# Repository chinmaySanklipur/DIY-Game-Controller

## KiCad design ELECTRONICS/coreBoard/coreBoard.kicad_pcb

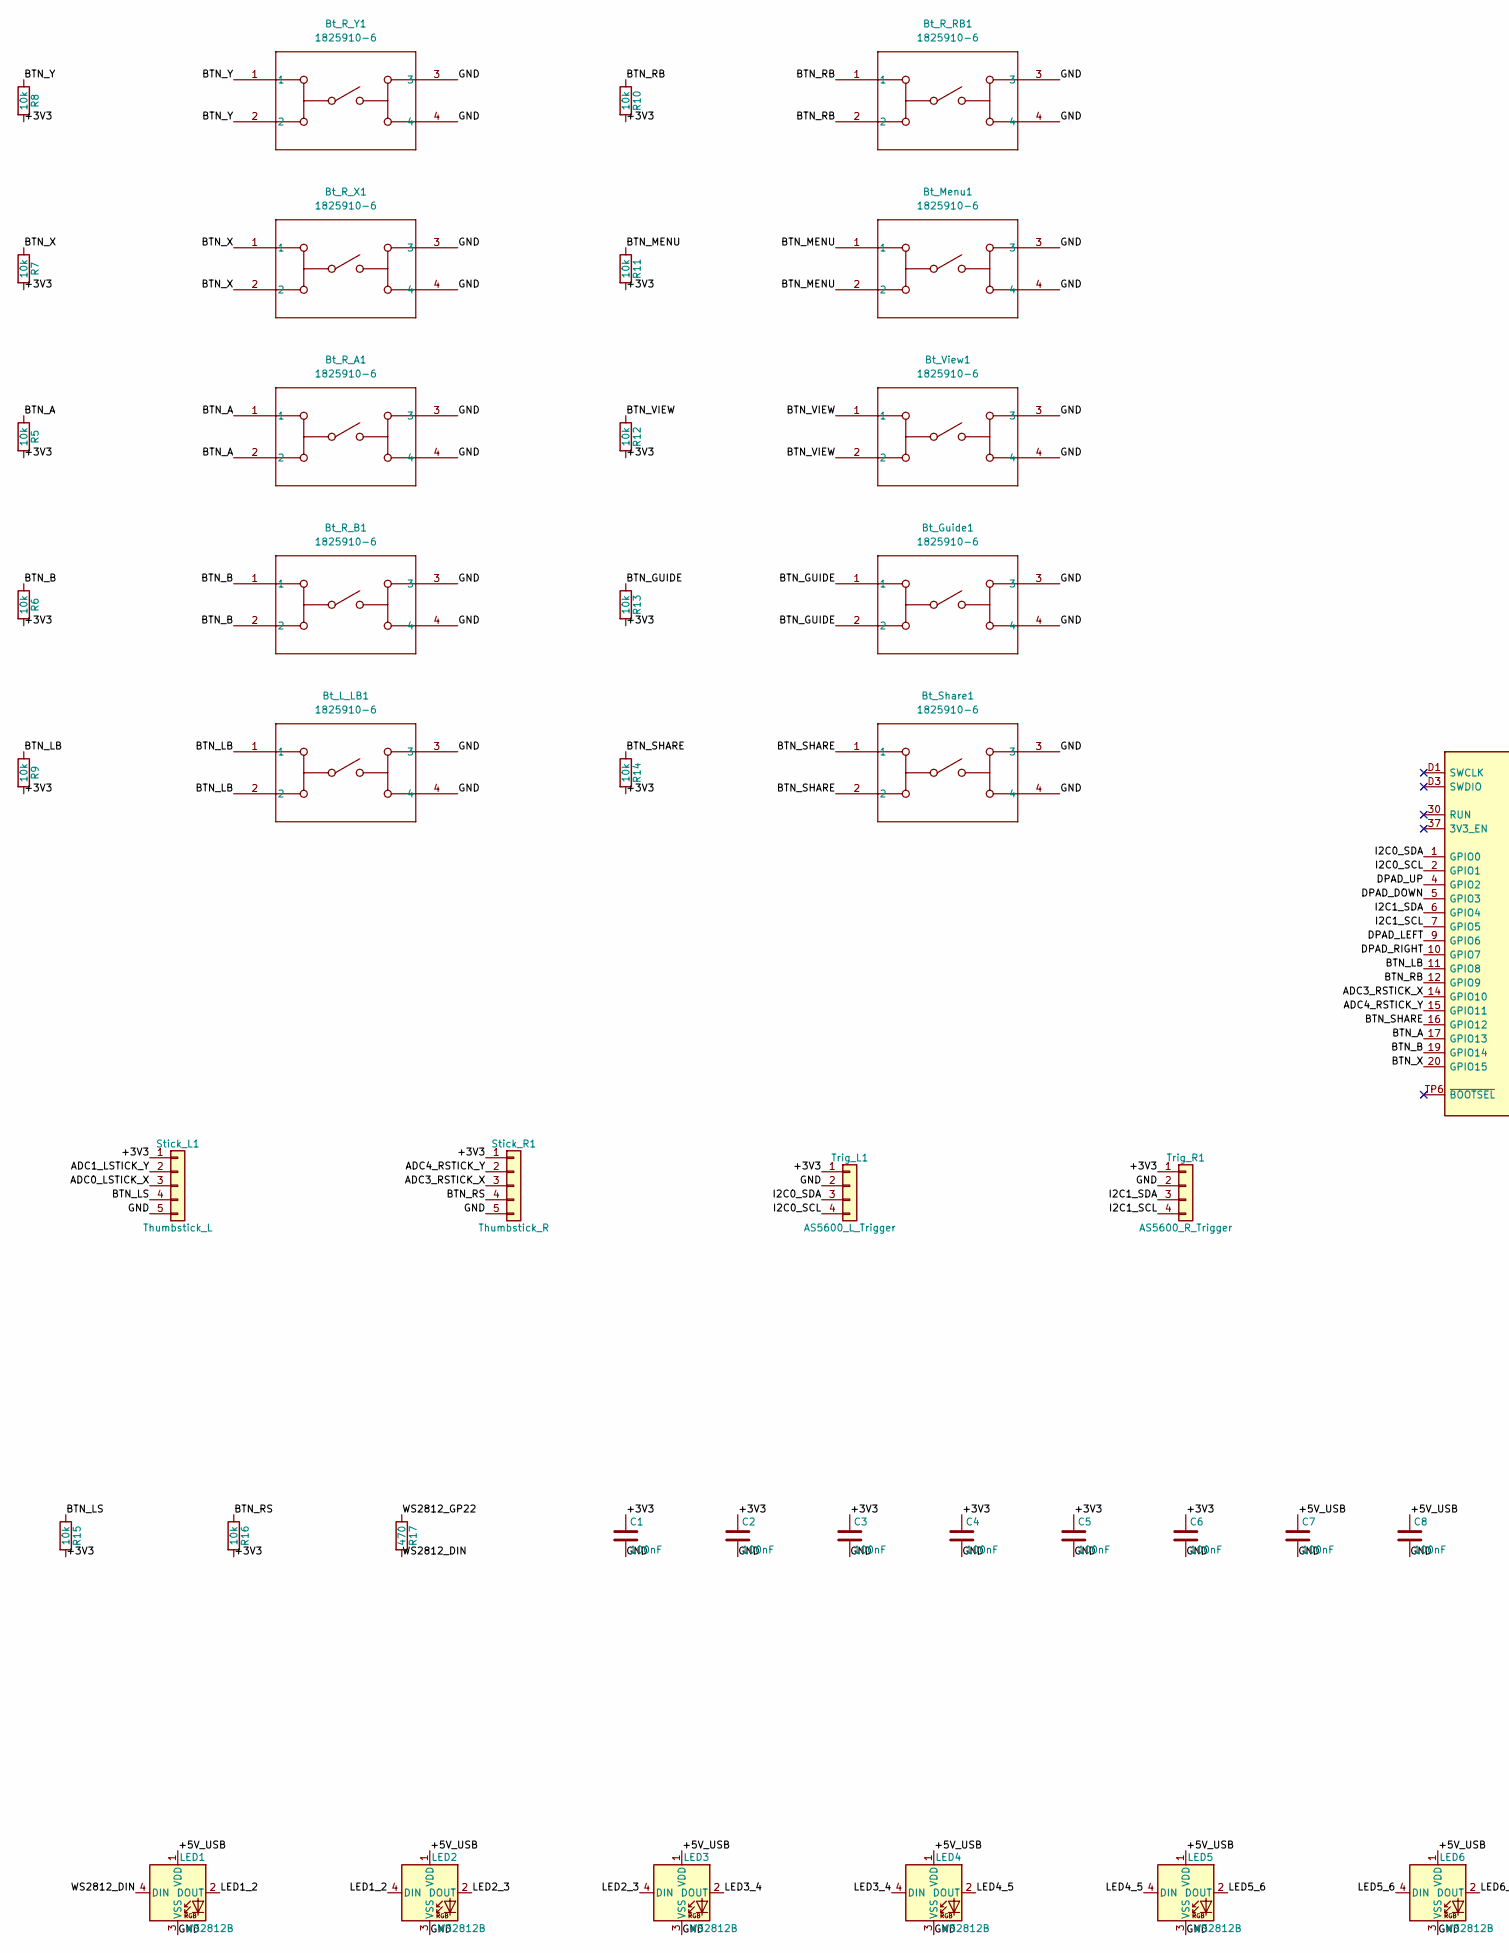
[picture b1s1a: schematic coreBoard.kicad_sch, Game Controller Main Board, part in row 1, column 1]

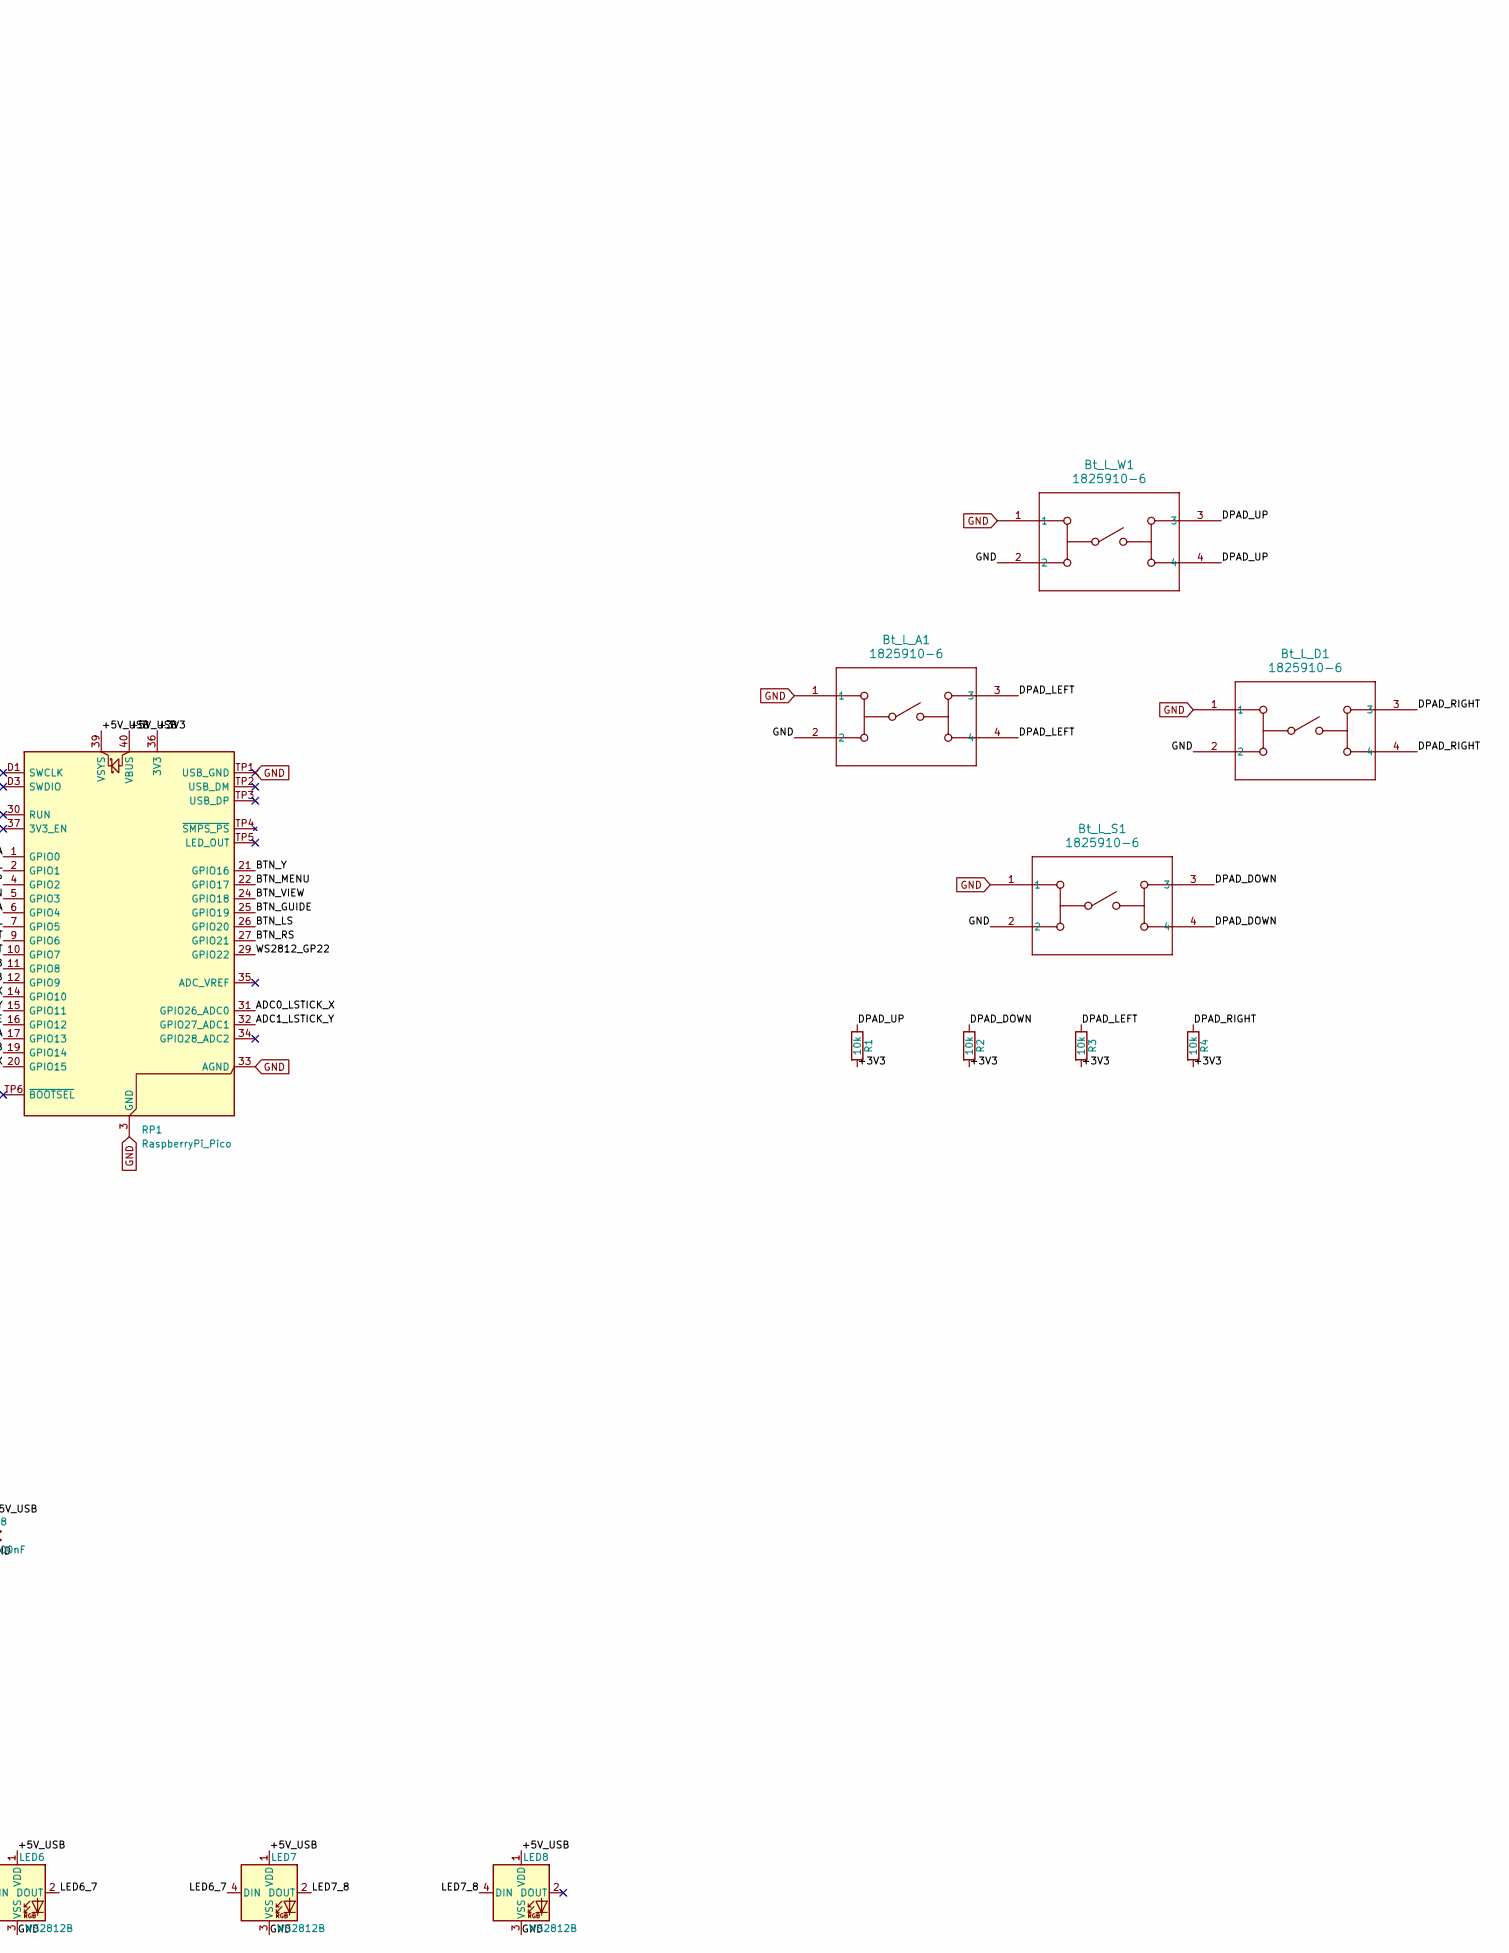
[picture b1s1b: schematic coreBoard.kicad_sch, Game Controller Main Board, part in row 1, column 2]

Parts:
Bt_Guide1: 1825910-6; SW4_1825910-B_TEC
Bt_L_A1: 1825910-6; SW4_1825910-B_TEC
Bt_L_D1: 1825910-6; SW4_1825910-B_TEC
Bt_L_LB1: 1825910-6; SW4_1825910-B_TEC
Bt_L_S1: 1825910-6; SW4_1825910-B_TEC
Bt_L_W1: 1825910-6; SW4_1825910-B_TEC
Bt_Menu1: 1825910-6; SW4_1825910-B_TEC
Bt_R_A1: 1825910-6; SW4_1825910-B_TEC
Bt_R_B1: 1825910-6; SW4_1825910-B_TEC
Bt_R_RB1: 1825910-6; SW4_1825910-B_TEC
Bt_R_X1: 1825910-6; SW4_1825910-B_TEC
Bt_R_Y1: 1825910-6; SW4_1825910-B_TEC
Bt_Share1: 1825910-6; SW4_1825910-B_TEC
Bt_View1: 1825910-6; SW4_1825910-B_TEC
C1, C2, C3, C4, C5, C6, C7, C8: 100nF; C_Disc_D5.0mm_W2.5mm_P5.00mm
LED1, LED2, LED3, LED4, LED5, LED6, LED7, LED8: WS2812B; LED_D5.0mm-4_RGB
R1, R2, R3, R4, R5, R6, R7, R8, R9, R10, R11, R12, R13, R14, R15, R16: 10k; R_Axial_DIN0207_L6.3mm_D2.5mm_P10.16mm_Horizontal
R17: 470; R_Axial_DIN0207_L6.3mm_D2.5mm_P10.16mm_Horizontal
RP1: RaspberryPi_Pico; RaspberryPi_Pico_SMD
Stick_L1: Thumbstick_L; PinHeader_1x05_P2.54mm_Vertical
Stick_R1: Thumbstick_R; PinHeader_1x05_P2.54mm_Vertical
Trig_L1: AS5600_L_Trigger; PinHeader_1x04_P2.54mm_Vertical
Trig_R1: AS5600_R_Trigger; PinHeader_1x04_P2.54mm_Vertical

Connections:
/+3V3: C1.1, C2.1, C3.1, C4.1, C5.1, C6.1, R1.2, R2.2, R3.2, R4.2, R5.2, R6.2, R7.2, R8.2, R9.2, R10.2, R11.2, R12.2, R13.2, R14.2, R15.2, R16.2, RP1.36 (3V3), Stick_L1.1, Stick_R1.1, Trig_L1.1, Trig_R1.1
/+5V_USB: C7.1, C8.1, LED1.1 (VDD), LED2.1 (VDD), LED3.1 (VDD), LED4.1 (VDD), LED5.1 (VDD), LED6.1 (VDD), LED7.1 (VDD), LED8.1 (VDD), RP1.39 (VSYS), RP1.40 (VBUS)
/ADC0_LSTICK_X: RP1.31 (GPIO26_ADC0), Stick_L1.3
/ADC1_LSTICK_Y: RP1.32 (GPIO27_ADC1), Stick_L1.2
/ADC3_RSTICK_X: RP1.14 (GPIO10), Stick_R1.3
/ADC4_RSTICK_Y: RP1.15 (GPIO11), Stick_R1.2
/BTN_A: Bt_R_A1.1, Bt_R_A1.2, R5.1, RP1.17 (GPIO13)
/BTN_B: Bt_R_B1.1, Bt_R_B1.2, R6.1, RP1.19 (GPIO14)
/BTN_GUIDE: Bt_Guide1.1, Bt_Guide1.2, R13.1, RP1.25 (GPIO19)
/BTN_LB: Bt_L_LB1.1, Bt_L_LB1.2, R9.1, RP1.11 (GPIO8)
/BTN_LS: R15.1, RP1.26 (GPIO20), Stick_L1.4
/BTN_MENU: Bt_Menu1.1, Bt_Menu1.2, R11.1, RP1.22 (GPIO17)
/BTN_RB: Bt_R_RB1.1, Bt_R_RB1.2, R10.1, RP1.12 (GPIO9)
/BTN_RS: R16.1, RP1.27 (GPIO21), Stick_R1.4
/BTN_SHARE: Bt_Share1.1, Bt_Share1.2, R14.1, RP1.16 (GPIO12)
/BTN_VIEW: Bt_View1.1, Bt_View1.2, R12.1, RP1.24 (GPIO18)
/BTN_X: Bt_R_X1.1, Bt_R_X1.2, R7.1, RP1.20 (GPIO15)
/BTN_Y: Bt_R_Y1.1, Bt_R_Y1.2, R8.1, RP1.21 (GPIO16)
/DPAD_DOWN: Bt_L_S1.3, Bt_L_S1.4, R2.1, RP1.5 (GPIO3)
/DPAD_LEFT: Bt_L_A1.3, Bt_L_A1.4, R3.1, RP1.9 (GPIO6)
/DPAD_RIGHT: Bt_L_D1.3, Bt_L_D1.4, R4.1, RP1.10 (GPIO7)
/DPAD_UP: Bt_L_W1.3, Bt_L_W1.4, R1.1, RP1.4 (GPIO2)
/I2C0_SCL: RP1.2 (GPIO1), Trig_L1.4
/I2C0_SDA: RP1.1 (GPIO0), Trig_L1.3
/I2C1_SCL: RP1.7 (GPIO5), Trig_R1.4
/I2C1_SDA: RP1.6 (GPIO4), Trig_R1.3
/LED1_2: LED1.2 (DOUT), LED2.4 (DIN)
/LED2_3: LED2.2 (DOUT), LED3.4 (DIN)
/LED3_4: LED3.2 (DOUT), LED4.4 (DIN)
/LED4_5: LED4.2 (DOUT), LED5.4 (DIN)
/LED5_6: LED5.2 (DOUT), LED6.4 (DIN)
/LED6_7: LED6.2 (DOUT), LED7.4 (DIN)
/LED7_8: LED7.2 (DOUT), LED8.4 (DIN)
/WS2812_DIN: LED1.4 (DIN), R17.2
/WS2812_GP22: R17.1, RP1.29 (GPIO22)
GND: Bt_Guide1.3, Bt_Guide1.4, Bt_L_A1.1, Bt_L_A1.2, Bt_L_D1.1, Bt_L_D1.2, Bt_L_LB1.3, Bt_L_LB1.4, Bt_L_S1.1, Bt_L_S1.2, Bt_L_W1.1, Bt_L_W1.2, Bt_Menu1.3, Bt_Menu1.4, Bt_R_A1.3, Bt_R_A1.4, Bt_R_B1.3, Bt_R_B1.4, Bt_R_RB1.3, Bt_R_RB1.4, Bt_R_X1.3, Bt_R_X1.4, Bt_R_Y1.3, Bt_R_Y1.4, Bt_Share1.3, Bt_Share1.4, Bt_View1.3, Bt_View1.4, C1.2, C2.2, C3.2, C4.2, C5.2, C6.2, C7.2, C8.2, LED1.3 (VSS), LED2.3 (VSS), LED3.3 (VSS), LED4.3 (VSS), LED5.3 (VSS), LED6.3 (VSS), LED7.3 (VSS), LED8.3 (VSS), RP1.3 (GND), RP1.8 (GND), RP1.13 (GND), RP1.18 (GND), RP1.23 (GND), RP1.28 (GND), RP1.33 (AGND), RP1.38 (GND), RP1.D2 (GND), RP1.TP1 (USB_GND), Stick_L1.5, Stick_R1.5, Trig_L1.2, Trig_R1.2

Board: 2 copper layers, 52 parts (0 on the bottom side), 36 nets, no tracks yet.

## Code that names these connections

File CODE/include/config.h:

/**
 * @file config.h
 * @brief Central configuration: GPIO pin assignments, timing, and tunable constants.
 *
 * Edit this file to remap pins or change deadzone/lighting behaviour.
 * Every other source file includes this header so changes here propagate
 * automatically at build time.
 *
 * Pin assignments mirror the KiCad schematic (game_controller.kicad_sch).
 * Net names in comments match schematic net labels for easy cross-reference.
 */

#ifndef CONFIG_H
#define CONFIG_H

#include "pico/stdlib.h"

/* ─────────────────────────────────────────────────────────────────────────────
 * GPIO — Digital Buttons
 * All buttons are active-LOW (pulled HIGH internally; pressed = connected to GND)
 * ───────────────────────────────────────────────────────────────────────────── */

/** Face buttons — schematic nets BTN_A … BTN_Y */
#define PIN_BTN_A       13   /* GP13 */
#define PIN_BTN_B       14   /* GP14 */
#define PIN_BTN_X       15   /* GP15 */
#define PIN_BTN_Y       16   /* GP16 */

/** D-pad — schematic nets DPAD_UP … DPAD_RIGHT */
#define PIN_DPAD_UP      2   /* GP2  */
#define PIN_DPAD_DN      3   /* GP3  */
#define PIN_DPAD_LEFT    6   /* GP6  */
#define PIN_DPAD_RIGHT   7   /* GP7  */

/** Bumpers — schematic nets BTN_LB / BTN_RB */
#define PIN_BTN_LB       8   /* GP8  */
#define PIN_BTN_RB       9   /* GP9  */

/** System buttons — schematic nets BTN_MENU / BTN_VIEW / BTN_GUIDE / BTN_SHARE */
#define PIN_BTN_MENU    17   /* GP17 */
#define PIN_BTN_VIEW    18   /* GP18 */
#define PIN_BTN_GUIDE   19   /* GP19 */
#define PIN_BTN_SHARE   12   /* GP12 */

/** Thumbstick click buttons — schematic nets BTN_LS / BTN_RS */
#define PIN_BTN_LS      20   /* GP20 */
#define PIN_BTN_RS      21   /* GP21 */

/* ─────────────────────────────────────────────────────────────────────────────
 * GPIO — Analog (ADC)
 * RP2040 ADC inputs are GP26-GP29.  Only GP26-GP28 are brought out on Pico.
 * Thumbstick axes are read on ADC0 and ADC1 (left stick).
 * ───────────────────────────────────────────────────────────────────────────── */

/** Left stick — schematic nets ADC0_LSTICK_X / ADC1_LSTICK_Y */
#define PIN_LSTICK_X    26   /* GP26 / ADC0 */
#define PIN_LSTICK_Y    27   /* GP27 / ADC1 */
#define ADC_LSTICK_X     0   /* ADC channel index for GP26 */
#define ADC_LSTICK_Y     1   /* ADC channel index for GP27 */

/**
 * Right stick — the Pico only exposes ADC on GP26-GP28, so the right stick
 * connects to GP10/GP11 read via external circuitry.  For this firmware we
 * treat these as the same two ADC channels multiplexed or read via the second
 * pair of physical lines.  Adjust if hardware differs.
 */
#define PIN_RSTICK_X    10   /* GP10 — right stick horizontal */
#define PIN_RSTICK_Y    11   /* GP11 — right stick vertical   */
/* Note: GP10/GP11 are NOT native ADC pins on RP2040.
 * If using a resistor-ladder or MCP3204 for right stick, replace ADC reads
 * in inputs.c with the appropriate SPI/I2C reads.
 * For a direct wiring option, swap thumbstick to GP26/GP27 for left and
 * route right stick via an external ADC IC. */

/* ─────────────────────────────────────────────────────────────────────────────
 * GPIO — I2C for AS5600 hall-effect trigger sensors
 * I2C0 → Left trigger  (U2, address 0x36)
 * I2C1 → Right trigger (U3, address 0x36 — separate bus avoids conflict)
 * ───────────────────────────────────────────────────────────────────────────── */

#define PIN_I2C0_SDA     0   /* GP0  — I2C0_SDA → U2 */
#define PIN_I2C0_SCL     1   /* GP1  — I2C0_SCL → U2 */
#define PIN_I2C1_SDA     4   /* GP4  — I2C1_SDA → U3 */
#define PIN_I2C1_SCL     5   /* GP5  — I2C1_SCL → U3 */

#define I2C_SPEED_HZ    400000   /* 400 kHz Fast-mode */
#define AS5600_ADDR     0x36     /* Fixed I2C address for AS5600 */
#define AS5600_REG_ANGLE_H 0x0C /* High byte of 12-bit raw angle */
#define AS5600_REG_ANGLE_L 0x0D /* Low  byte of 12-bit raw angle */

/* ─────────────────────────────────────────────────────────────────────────────
 * GPIO — WS2812B RGB LED data line
 * Uses PIO state machine so the CPU is never blocked during LED updates.
 * ───────────────────────────────────────────────────────────────────────────── */

#define PIN_WS2812      22   /* GP22 — WS2812_DIN through 470-ohm series R */
#define NUM_LEDS         8   /* LED1–LED8 in daisy-chain */
#define WS2812_PIO      pio0 /* Which PIO block to use */
#define WS2812_SM        0   /* State machine index within that PIO */

/* ─────────────────────────────────────────────────────────────────────────────
 * Deadzone and response-curve parameters
 * ───────────────────────────────────────────────────────────────────────────── */

/**
 * Inner circular deadzone radius as a fraction of the full stick range.
 * 0.08 = 8 % — deflections smaller than this produce zero output.
 * Prevents stick drift when the stick rests slightly off-centre.
 */
#define DEADZONE_INNER_FRAC   0.08f

/**
 * Outer clamp: values this close to maximum are treated as full deflection.
 * Compensates for sticks that do not mechanically reach true maximum.
 */
#define DEADZONE_OUTER_FRAC   0.97f

/**
 * Trigger inner dead-band: first N% of travel outputs zero.
 * Prevents accidental trigger input when the trigger rests slightly depressed.
 */
#define TRIGGER_INNER_FRAC    0.04f

/**
 * Trigger outer clamp: anything beyond this fraction is treated as fully pressed.
 */
#define TRIGGER_OUTER_FRAC    0.97f

/* ─────────────────────────────────────────────────────────────────────────────
 * ADC calibration storage keys in flash (littlefs)
 * ───────────────────────────────────────────────────────────────────────────── */

/** Path inside the littlefs volume where the config struct is stored */
#define CONFIG_FLASH_PATH  "/config.bin"

/** Magic number at start of stored config — detects uninitialised/corrupt data */
#define CONFIG_MAGIC  0xCAFE2026u

/* ─────────────────────────────────────────────────────────────────────────────
 * USB HID
 * ───────────────────────────────────────────────────────────────────────────── */

/** HID report interval in milliseconds (8 ms = 125 Hz, maximum for USB FS HID) */
#define HID_REPORT_INTERVAL_MS  8

/* ─────────────────────────────────────────────────────────────────────────────
 * Debounce
 * ───────────────────────────────────────────────────────────────────────────── */

/**
 * Number of consecutive identical readings required before a button state
 * change is accepted.  At a 1 kHz polling rate this gives a 3 ms debounce.
 */
#define DEBOUNCE_COUNT  3

#endif /* CONFIG_H */

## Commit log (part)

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2026-06-27 remove the ignore
2026-06-29 pico project
2026-06-29 organization
2026-06-29 some more organization
